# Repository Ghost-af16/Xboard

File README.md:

Its an RP2040 devboard which i make using the Guide which i can use in my projects 

**PCB**

**JLCPCB**

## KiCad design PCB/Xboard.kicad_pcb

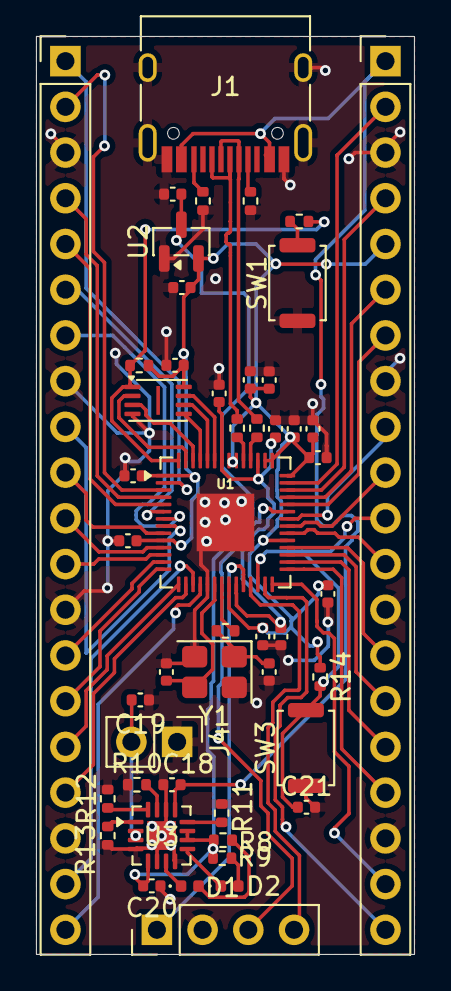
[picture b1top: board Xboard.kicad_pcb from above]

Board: 2 copper layers, 21.0 x 51.0 mm, 49 parts (0 on the bottom side), 63 nets.

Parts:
C1, C10, C18: 1uF; C_0402_1005Metric
C2, C3, C4, C5, C6, C7, C8, C9, C11, C12, C17, C21: 0.1uF; C_0402_1005Metric
C13, C14: 10uF; C_0402_1005Metric
C15, C16: 33pF; C_0402_1005Metric
C19, C20: 4.7uF; C_0402_1005Metric
D1, D2: LED; LED_0402_1005Metric
J1: USB_C_Receptacle_USB2.0_14P; USB_C_Receptacle_HRO_TYPE-C-31-M-12
J2, J3: Conn_01x20; PinHeader_1x20_P2.54mm_Vertical
J4: Conn_01x02; PinHeader_1x02_P2.54mm_Vertical
J5: Conn_01x04; PinHeader_1x04_P2.54mm_Vertical
R1, R2: 5.1k; R_0402_1005Metric
R3, R4: 27Ω; R_0402_1005Metric
R5: 1K; R_0402_1005Metric
R6, R14: 10k; R_0402_1005Metric
R7: 1k; R_0402_1005Metric
R8, R9: 1.5K; R_0402_1005Metric
R10: 4.12K; R_0402_1005Metric
R11: 1.18K; R_0402_1005Metric
R12: 1.13K; R_0402_1005Metric
R13: 10K; R_0402_1005Metric
SW1, SW3: SW_Push; SW_Push_SPST_NO_Alps_SKRK
U1: RP2040; QFN-56-1EP_7x7mm_P0.4mm_EP3.2x3.2mm
U2: MCP1700x-330xxTT; SOT-23
U3: BQ24074RGT; VQFN-16-1EP_3x3mm_P0.5mm_EP1.6x1.6mm
U4: W25Q16JVUXIQ TR; Winbond_USON-8-1EP_3x2mm_P0.5mm_EP0.2x1.6mm
Y1: 12 MHz; Crystal_SMD_3225-4Pin_3.2x2.5mm

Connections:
+1V1: C10.1, C11.1, C12.1, U1.23 (DVDD), U1.45 (VREG_VOUT), U1.50 (DVDD)
+3V3: C1.1, C2.1, C3.1, C4.1, C5.1, C6.1, C7.1, C8.1, C9.1, C14.1, C17.1, J3.5, R6.1, R14.1, U1.1 (IOVDD), U1.10 (IOVDD), U1.22 (IOVDD), U1.33 (IOVDD), U1.42 (IOVDD), U1.43 (ADC_AVDD), U1.44 (VREG_IN), U1.48 (USB_VDD), U1.49 (IOVDD), U2.2 (VO), U4.8 (VCC)
BQ_OUT: C13.1, C20.1, R8.1, R9.2, U2.3 (VI), U3.5 (EN2), U3.10 (OUT), U3.11 (OUT)
GND: C1.2, C2.2, C3.2, C4.2, C5.2, C6.2, C7.2, C8.2, C9.2, C10.2, C11.2, C12.2, C13.2, C14.2, C15.1, C16.1, C17.2, C18.1, C19.2, C20.2, C21.2, J1.A1 (GND), J1.A12 (GND), J1.B1 (GND), J1.B12 (GND), J1.S1 (SHIELD), J2.3, J2.8, J2.13, J2.18, J3.3, J3.8, J3.13, J3.18, J4.1, J5.2, R1.2, R2.2, R10.1, R11.1, R12.1, R13.2, SW1.1, SW3.1, U1.19 (TESTEN), U1.57 (GND), U2.1 (GND), U3.4 (~CE), U3.6 (EN1), U3.8 (VSS), U3.14 (TMR), U3.17 (VSS), U4.4 (GND), Y1.2, Y1.4
GPIO0: J2.1, U1.2 (GPIO0)
GPIO1: J2.2, U1.3 (GPIO1)
GPIO2: J2.4, U1.4 (GPIO2)
GPIO3: J2.5, U1.5 (GPIO3)
GPIO4: J2.6, U1.6 (GPIO4)
GPIO5: J2.7, U1.7 (GPIO5)
GPIO6: J2.9, U1.8 (GPIO6)
GPIO7: J2.10, U1.9 (GPIO7)
GPIO8: J2.11, U1.11 (GPIO8)
GPIO9: J2.12, U1.12 (GPIO9)
GPIO10: J2.14, U1.13 (GPIO10)
GPIO11: J2.15, U1.14 (GPIO11)
GPIO12: J2.16, U1.15 (GPIO12)
GPIO13: J2.17, U1.16 (GPIO13)
GPIO14: J2.19, U1.17 (GPIO14)
GPIO15: J2.20, U1.18 (GPIO15)
GPIO16: J3.20, U1.27 (GPIO16)
GPIO17: J3.19, U1.28 (GPIO17)
GPIO18: J3.17, U1.29 (GPIO18)
GPIO19: J3.16, U1.30 (GPIO19)
GPIO20: J3.15, U1.31 (GPIO20)
GPIO21: J3.14, U1.32 (GPIO21)
GPIO22: J3.12, U1.34 (GPIO22)
GPIO23: J3.10, U1.35 (GPIO23)
GPIO24: J3.9, U1.36 (GPIO24)
GPIO25: J5.3, U1.37 (GPIO25)
GPIO26_ADC0: J3.7, U1.38 (GPIO26_ADC0)
GPIO27_ADC1: J3.6, U1.39 (GPIO27_ADC1)
GPIO28_ADC2: J3.4, U1.40 (GPIO28_ADC2)
GPIO29_ADC3: J3.2, U1.41 (GPIO29_ADC3)
unnamed: C16.2, R5.1, Y1.1
unnamed: D1.2 (A), R8.2
unnamed: D1.1 (K), U3.7 (~PGOOD)
unnamed: D2.2 (A), R9.1
unnamed: D2.1 (K), U3.9 (~CHG)
unnamed: J1.A5 (CC1), R1.1
unnamed: J1.B5 (CC2), R2.1
unnamed: C19.1, J4.2, U3.2 (BAT), U3.3 (BAT)
unnamed: R7.1, SW1.2
unnamed: R4.2, U1.46 (USB_DM)
unnamed: R3.2, U1.47 (USB_DP)
unnamed: R11.2, U3.12 (ILIM)
unnamed: R12.2, U3.16 (ISET)
unnamed: R10.2, U3.15 (ITERM)
unnamed: R13.1, U3.1 (TS)
QSPI_SCLK: U1.52 (QSPI_SCLK), U4.6 (CLK)
QSPI_SD0: U1.53 (QSPI_SD0), U4.5 (DI/IO_{0})
QSPI_SD1: U1.55 (QSPI_SD1), U4.2 (DO/IO_{1})
QSPI_SD2: U1.54 (QSPI_SD2), U4.3 (~WP/IO_{2})
QSPI_SD3: U1.51 (QSPI_SD3), U4.7 (~HOLD/~RESET/IO_{3})
QSPI_SS: R6.2, R7.2, U1.56 (QSPI_SS), U4.1 (~CS)
RUN: C21.1, J3.11, R14.2, SW3.2, U1.26 (RUN)
SWD: J5.4, U1.25 (SWD)
SWDCLK: J5.1, U1.24 (SWCLK)
USB_D+: J1.A6 (D+), J1.B6 (D+), R3.1
USB_D-: J1.A7 (D-), J1.B7 (D-), R4.1
VBUS: C18.2, J1.A4 (VBUS), J1.A9 (VBUS), J1.B4 (VBUS), J1.B9 (VBUS), J3.1, U3.13 (IN)
XIN: C15.2, U1.20 (XIN), Y1.3
XOUT: R5.2, U1.21 (XOUT)

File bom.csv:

Designator,Footprint,Quantity,Value,LCSC Part #
"C1, C10, C18",0402,3,1uF,
"C11, C12, C17, C2, C21, C3, C4, C5, C6, C7, C8, C9",0402,12,0.1uF,
"C13, C14",0402,2,10uF,
"C15, C16",0402,2,33pF,
"C19, C20",0402,2,4.7uF,
"D1, D2",0402,2,LED,
J1,USB_C_Receptacle_HRO_TYPE-C-31-M-12,1,USB_C_Receptacle_USB2.0_14P,
"J2, J3",PinHeader_1x20_P2.54mm_Vertical,2,Conn_01x20,
J4,PinHeader_1x02_P2.54mm_Vertical,1,Conn_01x02,
J5,PinHeader_1x04_P2.54mm_Vertical,1,Conn_01x04,
"R1, R2",0402,2,5.1k,
R10,0402,1,4.12K,
R11,0402,1,1.18K,
R12,0402,1,1.13K,
"R13, R14, R6",0402,3,10K,
"R3, R4",0402,2,27Ω,
"R5, R7",0402,2,1K,
"R8, R9",0402,2,1.5K,
"SW1, SW3",SW_Push_SPST_NO_Alps_SKRK,2,SW_Push,
U1,QFN-56-1EP_7x7mm_P0.4mm_EP3.2x3.2mm,1,RP2040,
U2,SOT-23,1,MCP1700x-330xxTT,
U3,VQFN-16-1EP_3x3mm_P0.5mm_EP1.6x1.6mm,1,BQ24074RGT,
U4,Winbond_USON-8-1EP_3x2mm_P0.5mm_EP0.2x1.6mm,1,W25Q16JVUXIQ TR,
Y1,Crystal_SMD_3225-4Pin_3.2x2.5mm,1,12 MHz,
